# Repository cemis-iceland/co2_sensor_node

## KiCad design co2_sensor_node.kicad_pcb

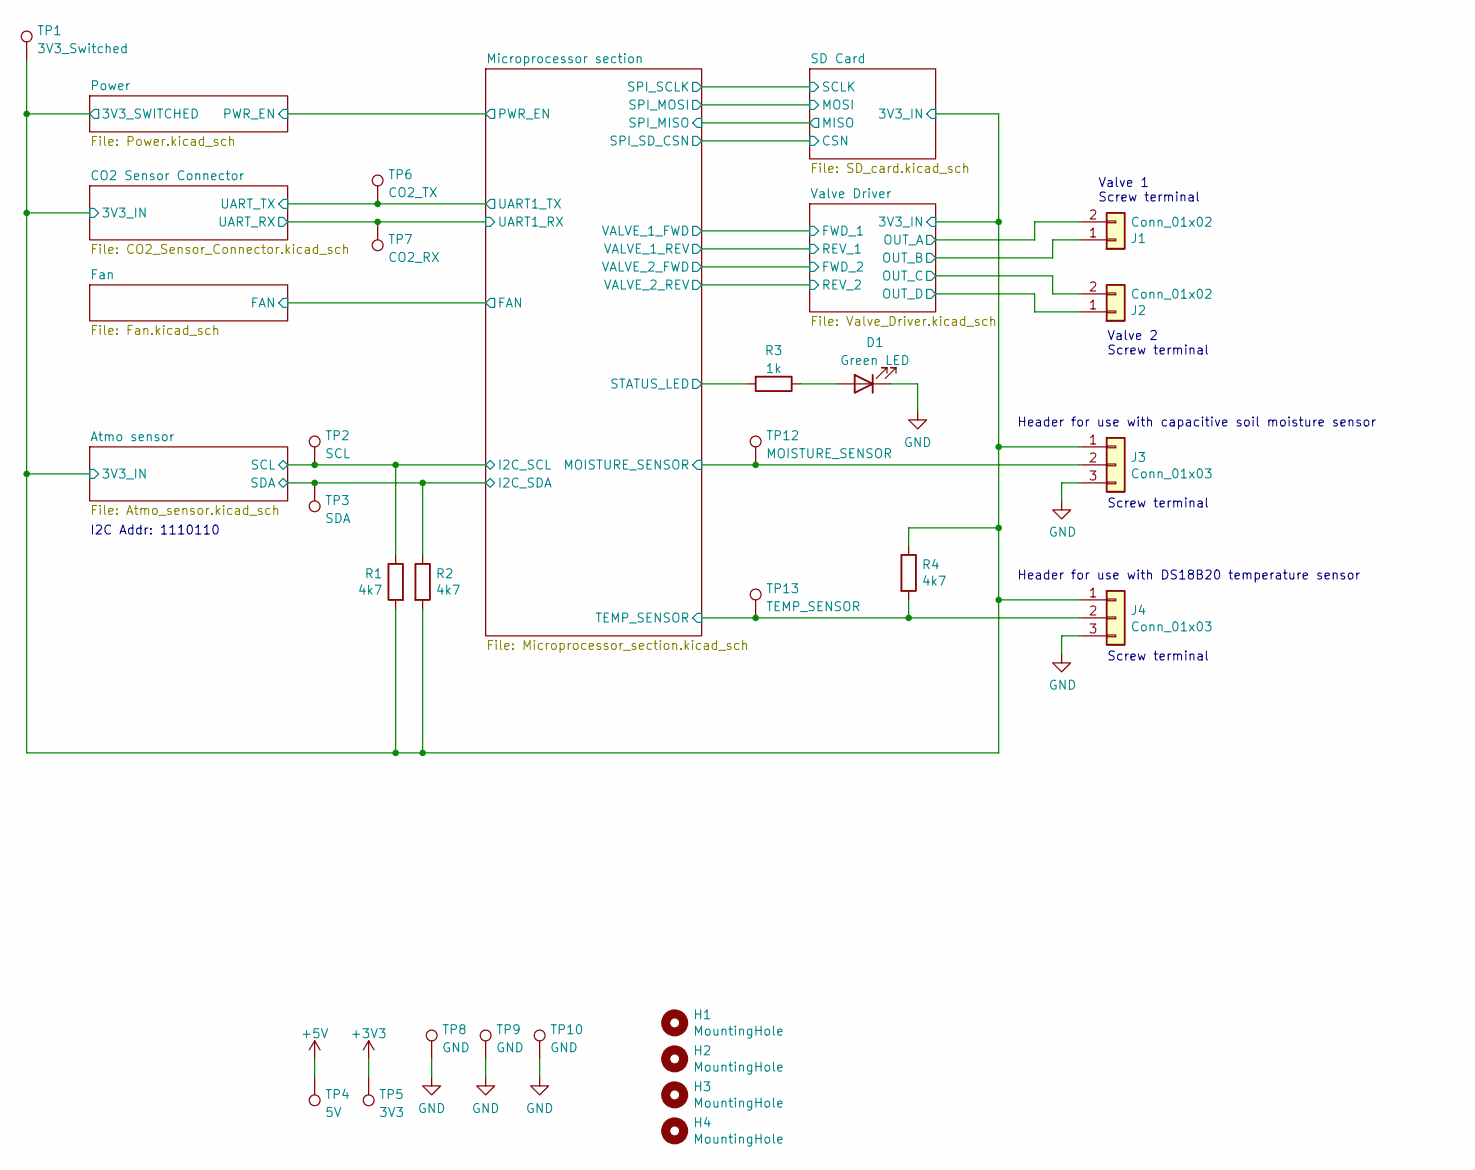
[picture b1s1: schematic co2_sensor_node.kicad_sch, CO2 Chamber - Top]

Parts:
D1: Green LED; LED_0603_1608Metric; LCSC C72043
H1, H2, H3, H4: MountingHole; MountingHole_3.2mm_M3
J1, J2: Conn_01x02; KF301-5.0-2P; LCSC C474881
J3, J4: Conn_01x03; KF301-5.0-3P; LCSC C474882
R1, R2, R4: 4k7; R_0603_1608Metric; LCSC C23162
R3: 1k; R_0603_1608Metric; LCSC C21190
TP1: 3V3_Switched; TestPoint_Loop_D2.50mm_Drill1.0mm_LowProfile
TP2: SCL; TestPoint_Loop_D2.50mm_Drill1.0mm_LowProfile
TP3: SDA; TestPoint_Loop_D2.50mm_Drill1.0mm_LowProfile
TP4: 5V; TestPoint_Loop_D2.50mm_Drill1.0mm_LowProfile
TP5: 3V3; TestPoint_Loop_D2.50mm_Drill1.0mm_LowProfile
TP6: CO2_TX; TestPoint_Loop_D2.50mm_Drill1.0mm_LowProfile
TP7: CO2_RX; TestPoint_Loop_D2.50mm_Drill1.0mm_LowProfile
TP8, TP9, TP10: GND; TestPoint_Loop_D2.50mm_Drill1.0mm_LowProfile
TP12: MOISTURE_SENSOR; TestPoint_Loop_D2.50mm_Drill1.0mm_LowProfile
TP13: TEMP_SENSOR; TestPoint_Loop_D2.50mm_Drill1.0mm_LowProfile

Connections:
+3V3: TP5.1; also elsewhere on the board
+5V: TP4.1; also elsewhere on the board
/Atmo sensor/3V3_IN: J3.1, J4.1, R1.2, R2.2, R4.1, TP1.1; also elsewhere on the board
/Atmo sensor/SCL: R1.1, TP2.1; also elsewhere on the board
/Atmo sensor/SDA: R2.1, TP3.1; also elsewhere on the board
/CO2 Sensor Connector/UART_RX: TP7.1; also elsewhere on the board
/CO2 Sensor Connector/UART_TX: TP6.1; also elsewhere on the board
/Microprocessor section/MOISTURE_SENSOR: J3.2, TP12.1; also elsewhere on the board
/Microprocessor section/STATUS_LED: R3.2; also elsewhere on the board
/Microprocessor section/TEMP_SENSOR: J4.2, R4.2, TP13.1; also elsewhere on the board
/Valve Driver/OUT_A: J1.2; also elsewhere on the board
/Valve Driver/OUT_B: J1.1; also elsewhere on the board
/Valve Driver/OUT_C: J2.2; also elsewhere on the board
/Valve Driver/OUT_D: J2.1; also elsewhere on the board
GND: D1.1 (K), J3.3, J4.3, TP8.1, TP9.1, TP10.1; also elsewhere on the board
unnamed: D1.2 (A), R3.1

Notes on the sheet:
I2C Addr: 1110110
Header for use with capacitive soil moisture sensor
Header for use with DS18B20 temperature sensor
Screw terminal
Valve 1 Screw terminal
Valve 2 Screw terminal

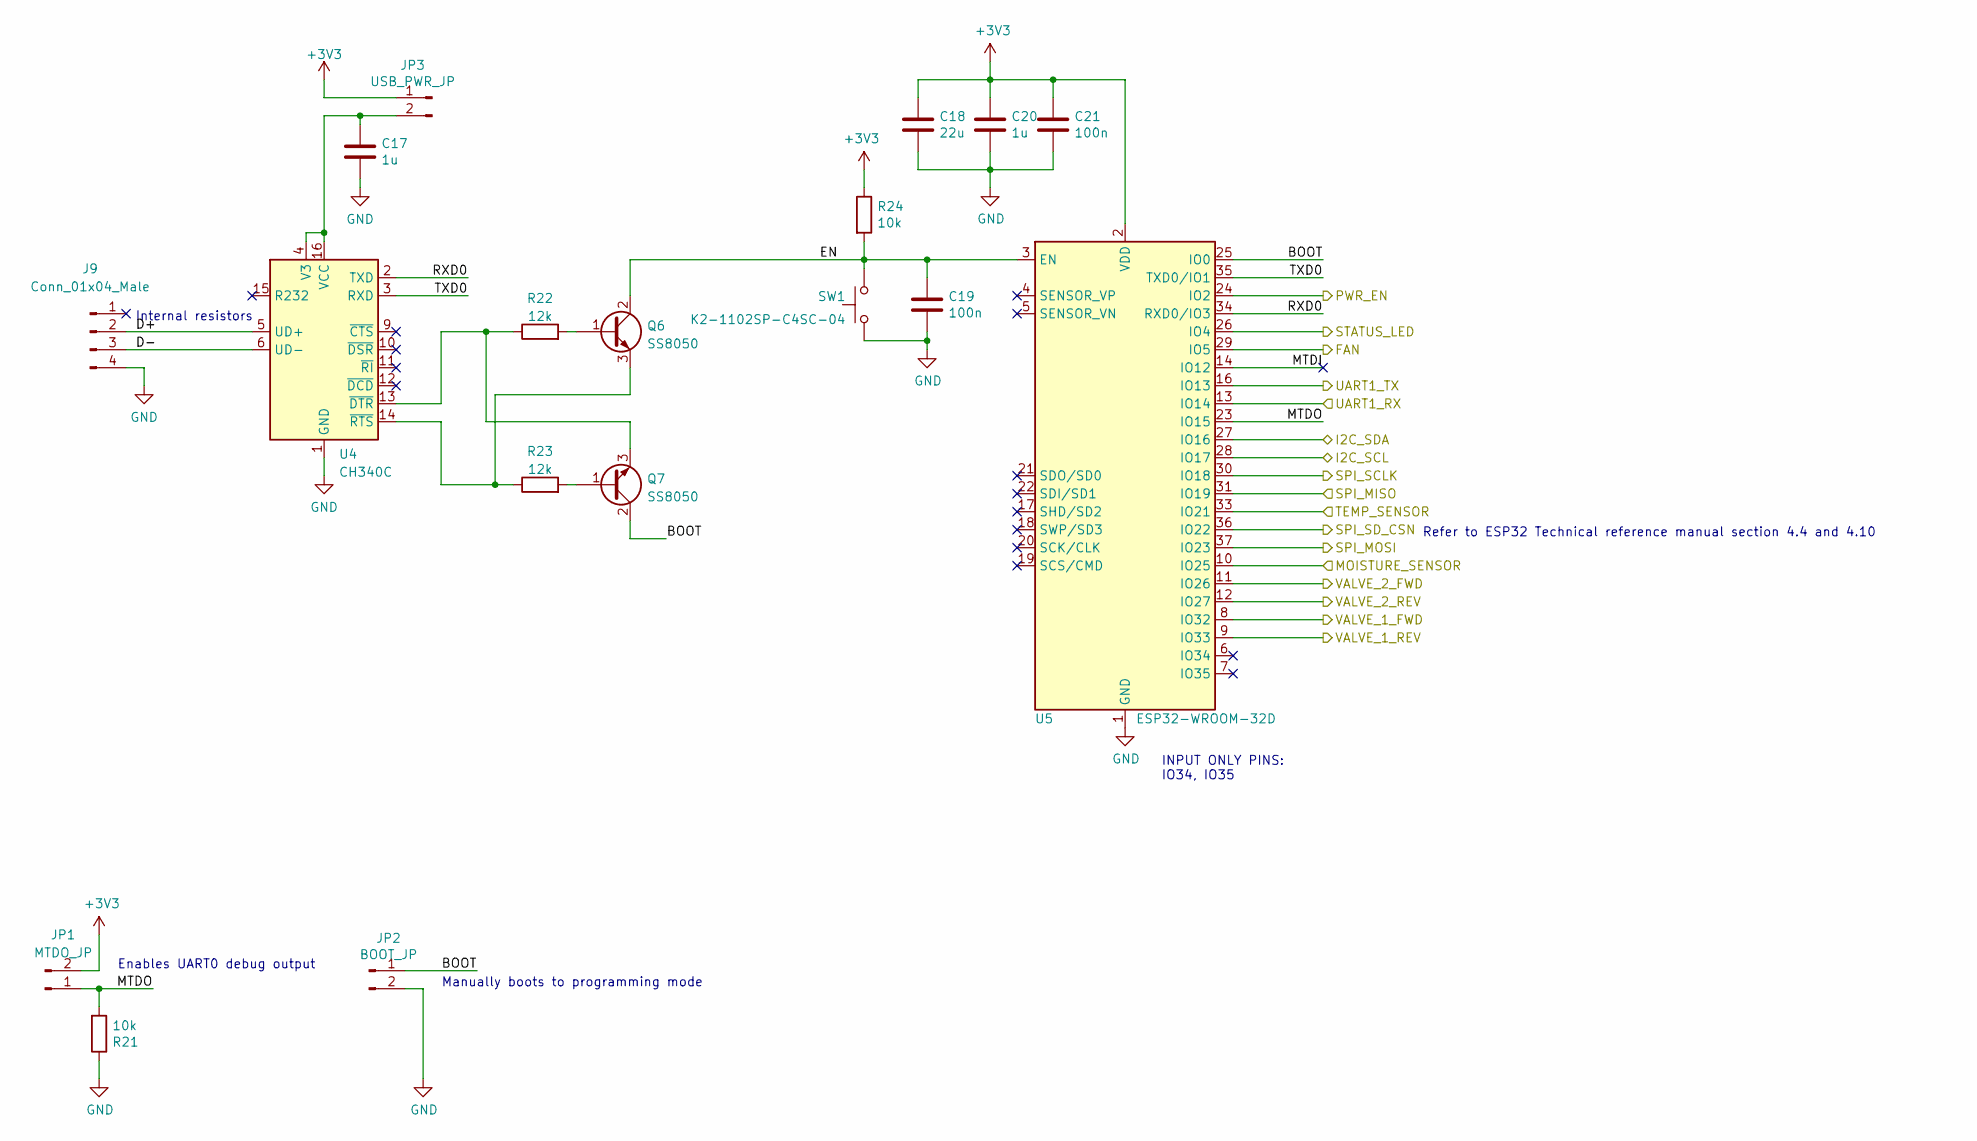
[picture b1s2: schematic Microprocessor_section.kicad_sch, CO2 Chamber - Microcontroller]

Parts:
C17, C20: 1u; C_0603_1608Metric; LCSC C15849
C18: 22u; C_0805_2012Metric; LCSC C45783
C19, C21: 100n; C_0603_1608Metric; LCSC C14663
J9: Conn_01x04_Male; PinHeader_1x04_P2.54mm_Vertical; LCSC C492403
JP1: MTDO_JP; PinHeader_1x02_P2.54mm_Vertical; LCSC C160332
JP2: BOOT_JP; PinHeader_1x02_P2.54mm_Vertical; LCSC C160332
JP3: USB_PWR_JP; PinHeader_1x02_P2.54mm_Vertical; LCSC C160332
Q6, Q7: SS8050; SOT-23; LCSC C2150
R21, R24: 10k; R_0603_1608Metric; LCSC C25804
R22, R23: 12k; R_0603_1608Metric; LCSC C22790
SW1: K2-1102SP-C4SC-04; K2-1102SP-xxxC; LCSC C127509
U4: CH340C; SOIC-16_3.9x9.9mm_P1.27mm; LCSC C84681
U5: ESP32-WROOM-32D; ESP32-WROOM-32; LCSC C473012

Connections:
+3V3: C18.1, C20.1, C21.1, JP1.2, JP3.1, R24.1, U5.2 (VDD); also elsewhere on the board
/Atmo sensor/SCL: U5.28 (IO17); also elsewhere on the board
/Atmo sensor/SDA: U5.27 (IO16); also elsewhere on the board
/CO2 Sensor Connector/UART_RX: U5.13 (IO14); also elsewhere on the board
/CO2 Sensor Connector/UART_TX: U5.16 (IO13); also elsewhere on the board
/Fan/FAN: U5.29 (IO5); also elsewhere on the board
/Microprocessor section/BOOT: JP2.1, Q7.2 (C), U5.25 (IO0)
/Microprocessor section/D+: J9.2, U4.5 (UD+)
/Microprocessor section/D-: J9.3, U4.6 (UD-)
/Microprocessor section/EN: C19.1, Q6.2 (C), R24.2, SW1.2, U5.3 (EN)
/Microprocessor section/MOISTURE_SENSOR: U5.10 (IO25); also elsewhere on the board
/Microprocessor section/MTDI: U5.14 (IO12)
/Microprocessor section/MTDO: JP1.1, R21.2, U5.23 (IO15)
/Microprocessor section/PWR_EN: U5.24 (IO2); also elsewhere on the board
/Microprocessor section/RXD0: U4.2 (TXD), U5.34 (RXD0/IO3)
/Microprocessor section/SPI_MISO: U5.31 (IO19); also elsewhere on the board
/Microprocessor section/SPI_MOSI: U5.37 (IO23); also elsewhere on the board
/Microprocessor section/SPI_SCLK: U5.30 (IO18); also elsewhere on the board
/Microprocessor section/SPI_SD_CSN: U5.36 (IO22); also elsewhere on the board
/Microprocessor section/STATUS_LED: U5.26 (IO4); also elsewhere on the board
/Microprocessor section/TEMP_SENSOR: U5.33 (IO21); also elsewhere on the board
/Microprocessor section/TXD0: U4.3 (RXD), U5.35 (TXD0/IO1)
/Microprocessor section/VALVE_1_FWD: U5.8 (IO32); also elsewhere on the board
/Microprocessor section/VALVE_1_REV: U5.9 (IO33); also elsewhere on the board
/Microprocessor section/VALVE_2_FWD: U5.11 (IO26); also elsewhere on the board
/Microprocessor section/VALVE_2_REV: U5.12 (IO27); also elsewhere on the board
GND: C17.2, C18.2, C19.2, C20.2, C21.2, J9.4, JP2.2, R21.1, SW1.1, U4.1 (GND), U5.1 (GND), U5.15 (GND), U5.38 (GND), U5.39 (GND); also elsewhere on the board
unnamed: C17.1, JP3.2, U4.4 (V3), U4.16 (VCC)
unnamed: Q6.1 (B), R22.2
unnamed: Q6.3 (E), R23.1, U4.14 (~RTS)
unnamed: Q7.1 (B), R23.2
unnamed: Q7.3 (E), R22.1, U4.13 (~DTR)

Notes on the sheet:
INPUT ONLY PINS: IO34, IO35
Refer to ESP32 Technical reference manual section 4.4 and 4.10
Internal resistors
Manually boots to programming mode
Enables UART0 debug output

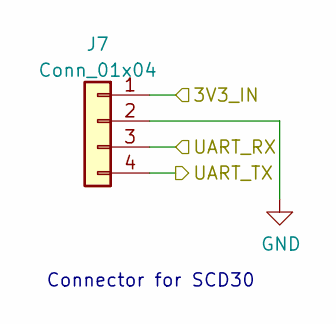
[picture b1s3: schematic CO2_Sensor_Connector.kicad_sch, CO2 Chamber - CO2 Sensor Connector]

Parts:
J7: Conn_01x04; JST_XH_B4B-XH-A_1x04_P2.50mm_Vertical; LCSC C37815

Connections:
/Atmo sensor/3V3_IN: J7.1; also elsewhere on the board
/CO2 Sensor Connector/UART_RX: J7.3; also elsewhere on the board
/CO2 Sensor Connector/UART_TX: J7.4; also elsewhere on the board
GND: J7.2; also elsewhere on the board

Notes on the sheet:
Connector for SCD30

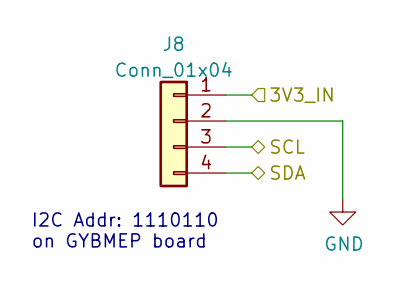
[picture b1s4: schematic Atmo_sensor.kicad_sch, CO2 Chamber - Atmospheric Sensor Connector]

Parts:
J8: Conn_01x04; JST_XH_B4B-XH-A_1x04_P2.50mm_Vertical; LCSC C37815

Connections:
/Atmo sensor/3V3_IN: J8.1; also elsewhere on the board
/Atmo sensor/SCL: J8.3; also elsewhere on the board
/Atmo sensor/SDA: J8.4; also elsewhere on the board
GND: J8.2; also elsewhere on the board

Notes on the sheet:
I2C Addr: 1110110 on GYBMEP board

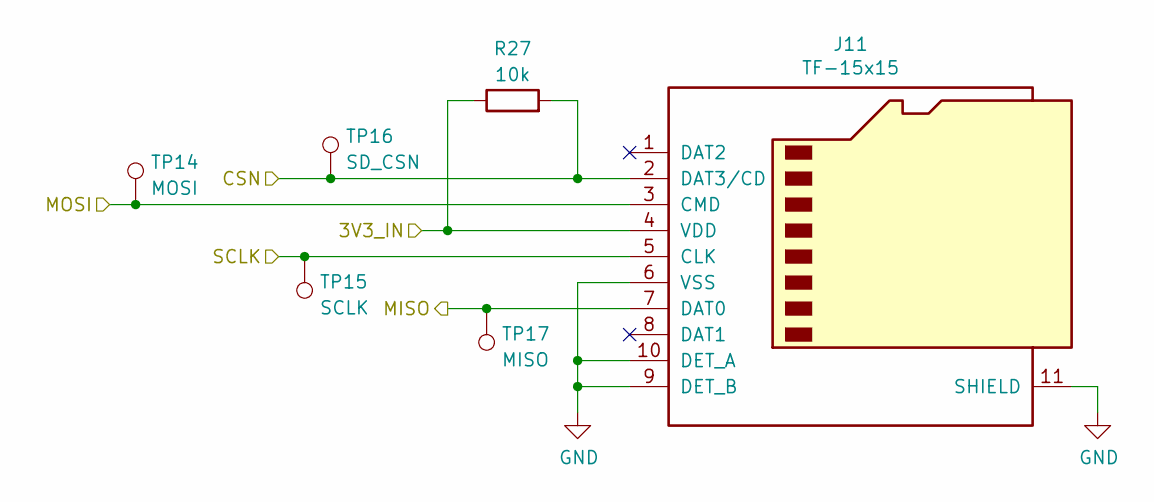
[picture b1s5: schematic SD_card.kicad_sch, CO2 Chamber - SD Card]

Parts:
J11: TF-15x15; LCSC C111196
R27: 10k; R_0603_1608Metric; LCSC C25804
TP14: MOSI; TestPoint_Loop_D2.50mm_Drill1.0mm_LowProfile
TP15: SCLK; TestPoint_Loop_D2.50mm_Drill1.0mm_LowProfile
TP16: SD_CSN; TestPoint_Loop_D2.50mm_Drill1.0mm_LowProfile
TP17: MISO; TestPoint_Loop_D2.50mm_Drill1.0mm_LowProfile

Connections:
/Atmo sensor/3V3_IN: J11.4 (VDD), R27.1; also elsewhere on the board
/Microprocessor section/SPI_MISO: J11.7 (DAT0), TP17.1; also elsewhere on the board
/Microprocessor section/SPI_MOSI: J11.3 (CMD), TP14.1; also elsewhere on the board
/Microprocessor section/SPI_SCLK: J11.5 (CLK), TP15.1; also elsewhere on the board
/Microprocessor section/SPI_SD_CSN: J11.2 (DAT3/CD), R27.2, TP16.1; also elsewhere on the board
GND: J11.6 (VSS), J11.9 (DET_B), J11.10 (DET_A), J11.11 (SHIELD); also elsewhere on the board

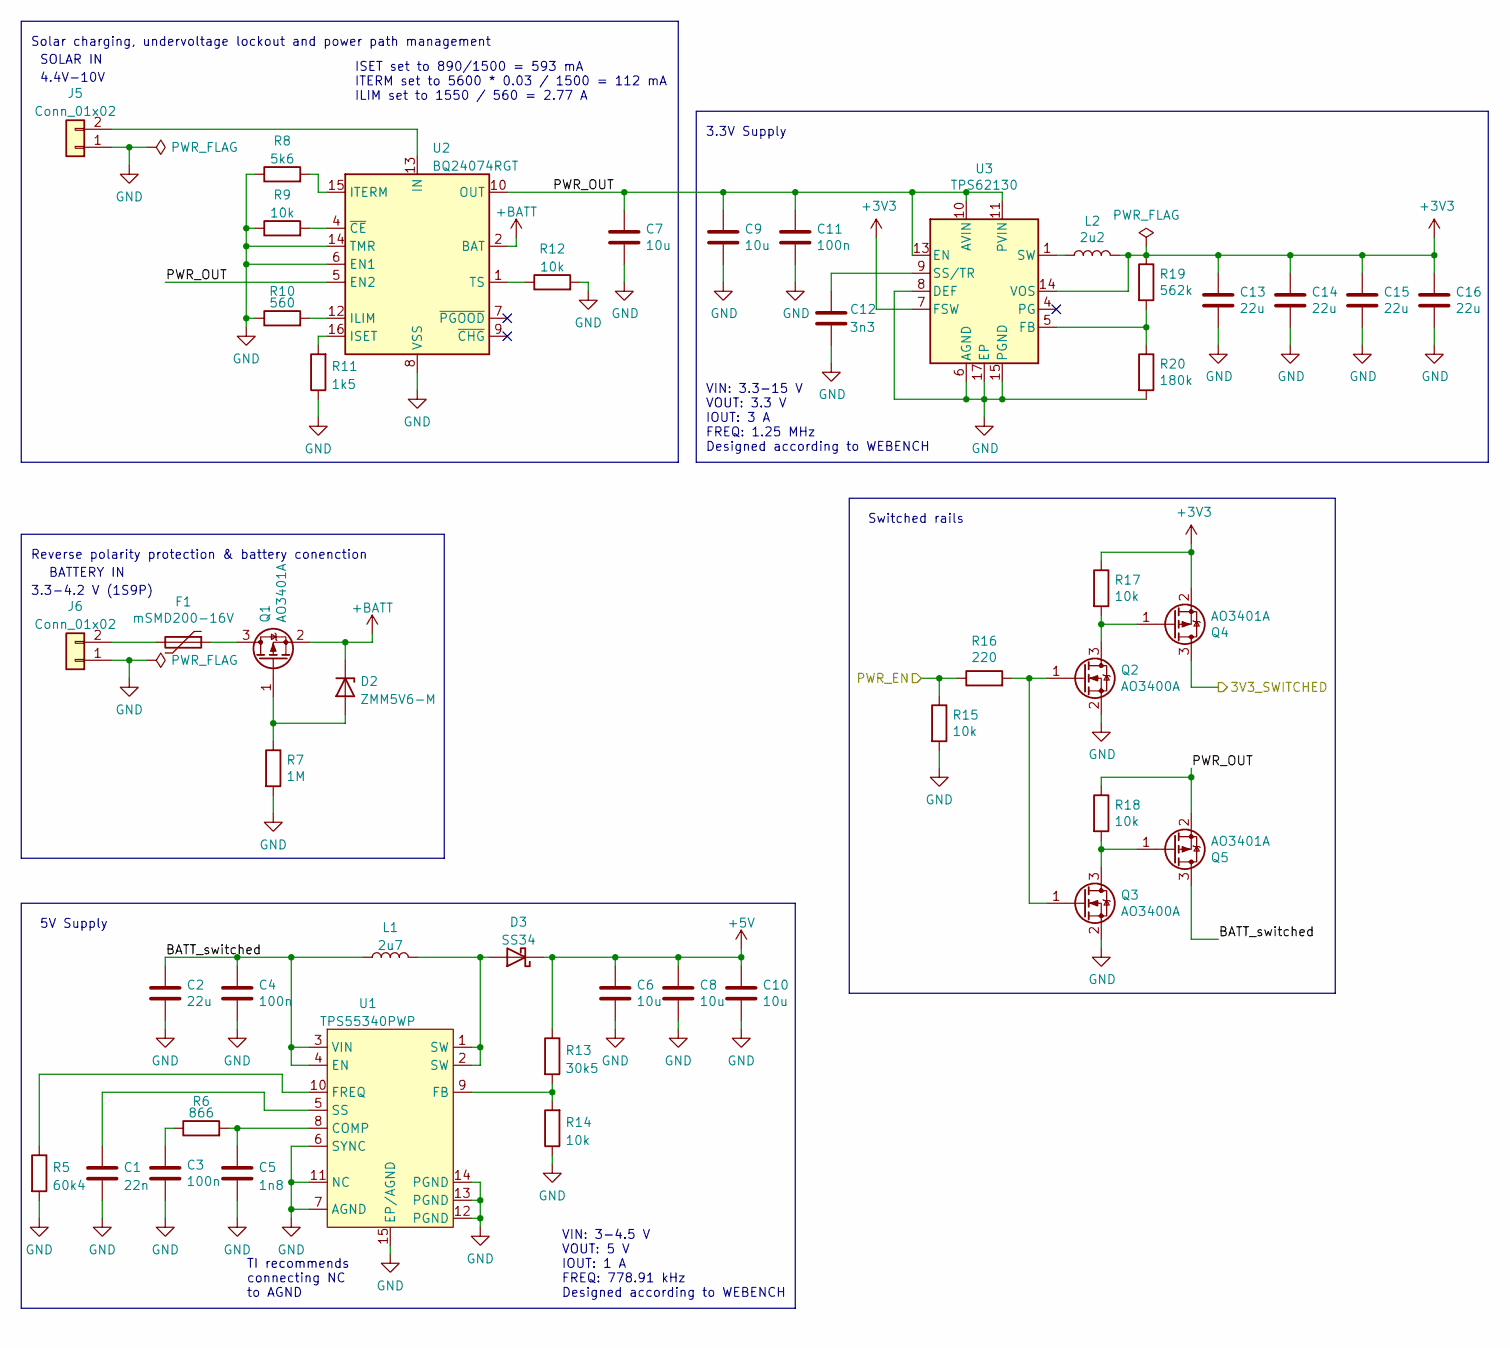
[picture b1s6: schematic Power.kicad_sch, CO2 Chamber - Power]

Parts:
C1: 22n; C_0603_1608Metric; LCSC C21122
C2, C13, C14, C15, C16: 22u; C_0805_2012Metric; LCSC C45783
C3, C4, C11: 100n; C_0603_1608Metric; LCSC C14663
C5: 1n8; C_0603_1608Metric; LCSC C318642
C6, C7, C8, C9, C10: 10u; C_0805_2012Metric; LCSC C15850
C12: 3n3; C_0603_1608Metric; LCSC C1613
D2: ZMM5V6-M; D_MiniMELF; LCSC C8062
D3: SS34; D_SMA; LCSC C8678
F1: mSMD200-16V; Fuse_1812_4532Metric; LCSC C70126
J5, J6: Conn_01x02; JST_XH_B2B-XH-AM_1x02_P2.50mm_Vertical; LCSC C20079
L1: 2u7; PCD0504MT2R7; LCSC C324320
L2: 2u2; WPN4020; LCSC C98361
Q1, Q4, Q5: AO3401A; SOT-23; LCSC C15127
Q2, Q3: AO3400A; SOT-23; LCSC C20917
R5: 60k4; R_0402_1005Metric; LCSC C310240
R6: 866; R_0402_1005Metric; LCSC C227251
R7: 1M; R_0603_1608Metric; LCSC C22935
R8: 5k6; R_0603_1608Metric
R9, R12, R14, R15, R17, R18: 10k; R_0603_1608Metric; LCSC C25804
R10: 560; R_0603_1608Metric
R11: 1k5; R_0603_1608Metric
R13: 30k5; R_0402_1005Metric; LCSC C185428
R16: 220; R_0603_1608Metric; LCSC C22962
R19: 562k; R_0603_1608Metric; LCSC C23205
R20: 180k; R_0603_1608Metric; LCSC C22827
U1: TPS55340PWP; HTSSOP-14-1EP_4.4x5mm_P0.65mm_EP3.4x5mm_Mask3x3.1mm_Thermal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; LCSC C43862
U2: BQ24074RGT; VQFN-16-1EP_3x3mm_P0.5mm_EP1.6x1.6mm; LCSC C54313
U3: TPS62130; VQFN-16-1EP_3x3mm_P0.5mm_EP1.68x1.68mm_ThermalVias; LCSC C43590

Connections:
+3V3: C13.1, C14.1, C15.1, C16.1, L2.2, Q4.2 (S), R17.1, R19.1, U3.7 (FSW), U3.14 (VOS); also elsewhere on the board
+5V: C6.1, C8.1, C10.1, D3.1 (K), R13.1; also elsewhere on the board
+BATT: D2.1 (K), Q1.2 (S), U2.2 (BAT), U2.3 (BAT)
/Atmo sensor/3V3_IN: Q4.3 (D); also elsewhere on the board
/Microprocessor section/PWR_EN: R15.1, R16.1; also elsewhere on the board
/Power/BATT_switched: C2.1, C4.1, L1.1, Q5.3 (D), U1.3 (VIN), U1.4 (EN)
/Power/PWR_OUT: C7.1, C9.1, C11.1, Q5.2 (S), R18.1, U2.5 (EN2), U2.10 (OUT), U2.11 (OUT), U3.10 (AVIN), U3.11 (PVIN), U3.12 (PVIN), U3.13 (EN)
GND: C1.2, C2.2, C3.2, C4.2, C5.2, C6.2, C7.2, C8.2, C9.2, C10.2, C11.2, C12.2, C13.2, C14.2, C15.2, C16.2, J5.1, J6.1, Q2.2 (S), Q3.2 (S), R5.2, R7.2, R8.1, R9.1, R10.1, R11.1, R12.2, R14.1, R15.2, R20.2, U1.6 (SYNC), U1.7 (AGND), U1.11 (NC), U1.12 (PGND), U1.13 (PGND), U1.14 (PGND), U1.15 (EP/AGND), U2.6 (EN1), U2.8 (VSS), U2.14 (TMR), U2.17 (VSS), U3.6 (AGND), U3.8 (DEF), U3.15 (PGND), U3.16 (PGND), U3.17 (EP); also elsewhere on the board
unnamed: C1.1, U1.5 (SS)
unnamed: C3.1, R6.1
unnamed: C5.1, R6.2, U1.8 (COMP)
unnamed: C12.1, U3.9 (SS/TR)
unnamed: D2.2 (A), Q1.1 (G), R7.1
unnamed: D3.2 (A), L1.2, U1.1 (SW), U1.2 (SW)
unnamed: F1.1, Q1.3 (D)
unnamed: F1.2, J6.2
unnamed: J5.2, U2.13 (IN)
unnamed: L2.1, U3.1 (SW), U3.2 (SW), U3.3 (SW)
unnamed: Q2.1 (G), Q3.1 (G), R16.2
unnamed: Q2.3 (D), Q4.1 (G), R17.2
unnamed: Q3.3 (D), Q5.1 (G), R18.2
unnamed: R5.1, U1.10 (FREQ)
unnamed: R8.2, U2.15 (ITERM)
unnamed: R9.2, U2.4 (~CE)
unnamed: R10.2, U2.12 (ILIM)
unnamed: R11.2, U2.16 (ISET)
unnamed: R12.1, U2.1 (TS)
unnamed: R13.2, R14.2, U1.9 (FB)
unnamed: R19.2, R20.1, U3.5 (FB)

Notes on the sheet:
VIN: 3.3-15 V VOUT: 3.3 V IOUT: 3 A FREQ: 1.25 MHz Designed according to WEBENCH
BATTERY IN
5V Supply
4.4V-10V
Solar charging, undervoltage lockout and power path management
3.3-4.2 V (1S9P)
3.3V Supply
Reverse polarity protection & battery conenction
SOLAR IN
ISET set to 890/1500 = 593 mA ITERM set to 5600 * 0.03 / 1500 = 112 mA ILIM set to 1550 / 560 = 2.77 A
VIN: 3-4.5 V VOUT: 5 V IOUT: 1 A FREQ: 778.91 kHz Designed according to WEBENCH
TI recommends connecting NC to AGND
Switched rails

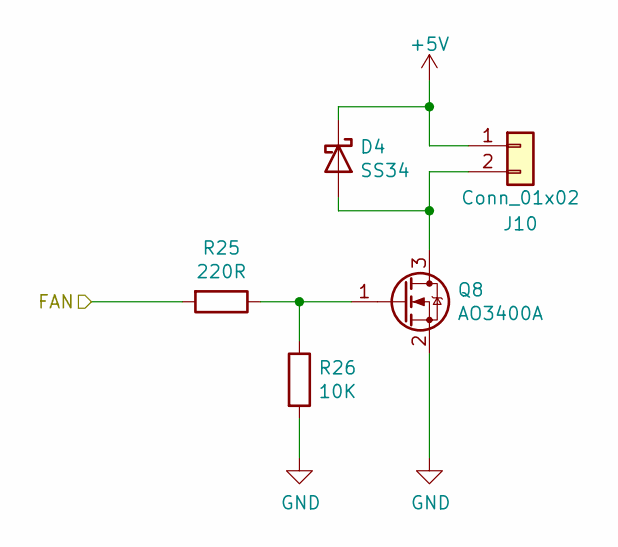
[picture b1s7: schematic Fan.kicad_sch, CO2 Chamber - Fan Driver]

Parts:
D4: SS34; D_SMA; LCSC C8678
J10: Conn_01x02; JST_XH_B2B-XH-AM_1x02_P2.50mm_Vertical; LCSC C20079
Q8: AO3400A; SOT-23; LCSC C20917
R25: 220R; R_0603_1608Metric
R26: 10K; R_0603_1608Metric

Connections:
+5V: D4.1 (K), J10.1; also elsewhere on the board
/Fan/FAN: R25.2; also elsewhere on the board
GND: Q8.2 (S), R26.2; also elsewhere on the board
unnamed: D4.2 (A), J10.2, Q8.3 (D)
unnamed: Q8.1 (G), R25.1, R26.1

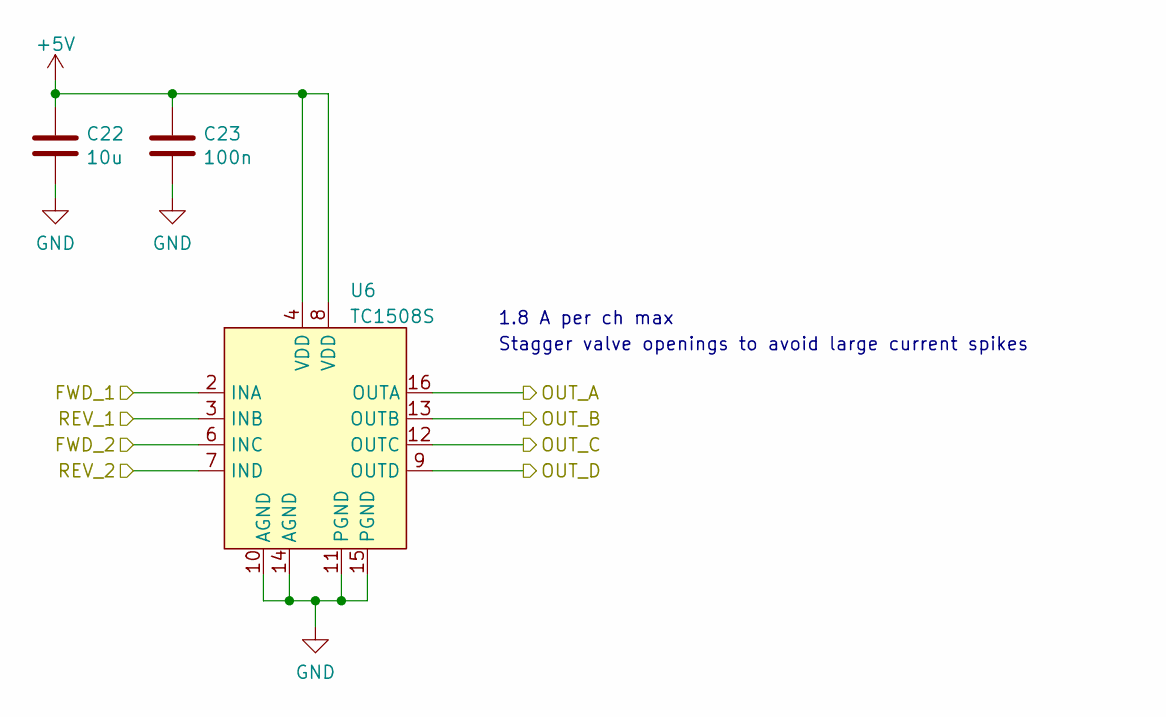
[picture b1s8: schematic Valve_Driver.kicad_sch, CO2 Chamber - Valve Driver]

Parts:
C22: 10u; C_0805_2012Metric; LCSC C15850
C23: 100n; C_0603_1608Metric; LCSC C14663
U6: TC1508S; SOP-16_3.9x9.9mm_P1.27mm; LCSC C89480

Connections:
+5V: C22.1, C23.1, U6.4 (VDD), U6.8 (VDD); also elsewhere on the board
/Microprocessor section/VALVE_1_FWD: U6.2 (INA); also elsewhere on the board
/Microprocessor section/VALVE_1_REV: U6.3 (INB); also elsewhere on the board
/Microprocessor section/VALVE_2_FWD: U6.6 (INC); also elsewhere on the board
/Microprocessor section/VALVE_2_REV: U6.7 (IND); also elsewhere on the board
/Valve Driver/OUT_A: U6.16 (OUTA); also elsewhere on the board
/Valve Driver/OUT_B: U6.13 (OUTB); also elsewhere on the board
/Valve Driver/OUT_C: U6.12 (OUTC); also elsewhere on the board
/Valve Driver/OUT_D: U6.9 (OUTD); also elsewhere on the board
GND: C22.2, C23.2, U6.10 (AGND), U6.11 (PGND), U6.14 (AGND), U6.15 (PGND); also elsewhere on the board

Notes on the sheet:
1.8 A per ch max
Stagger valve openings to avoid large current spikes

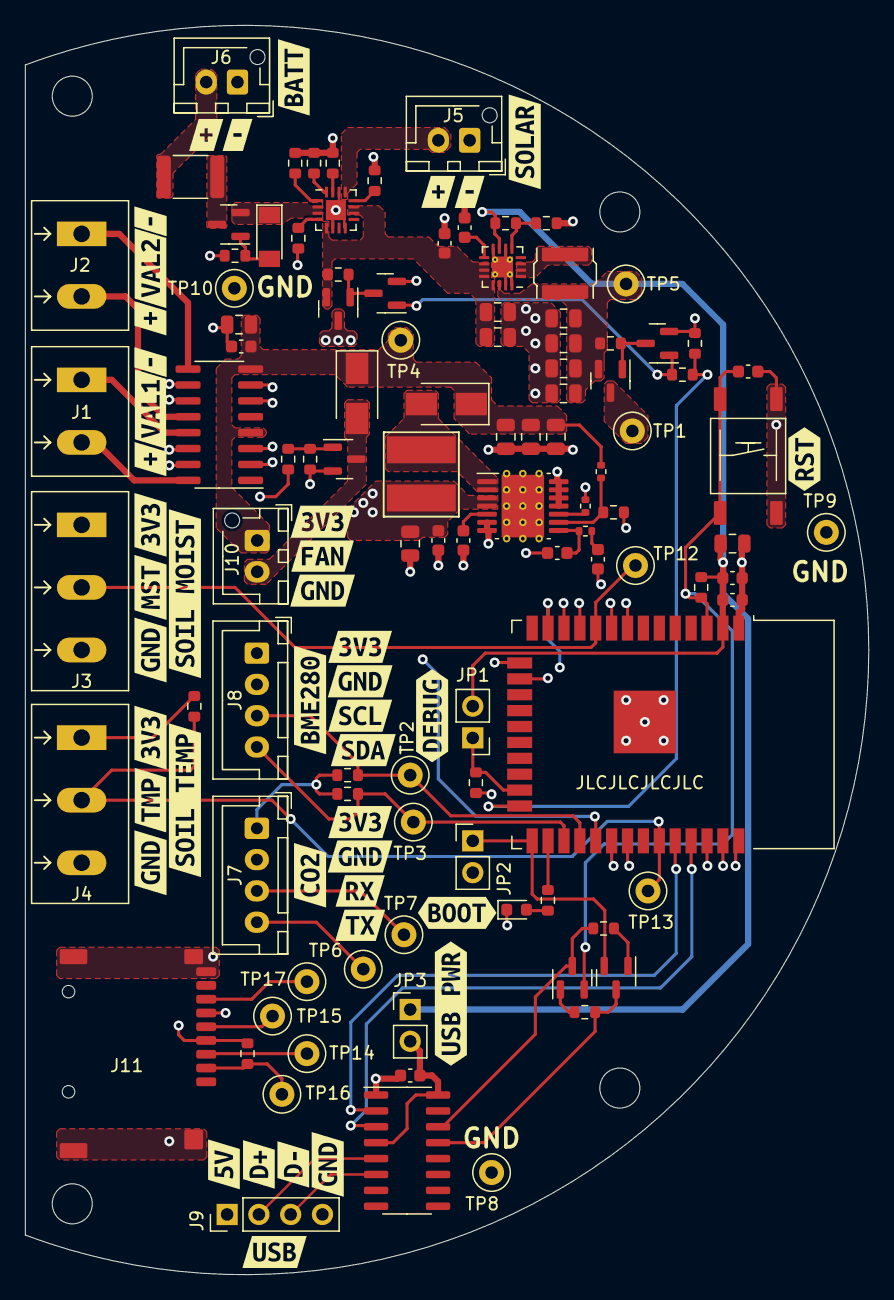
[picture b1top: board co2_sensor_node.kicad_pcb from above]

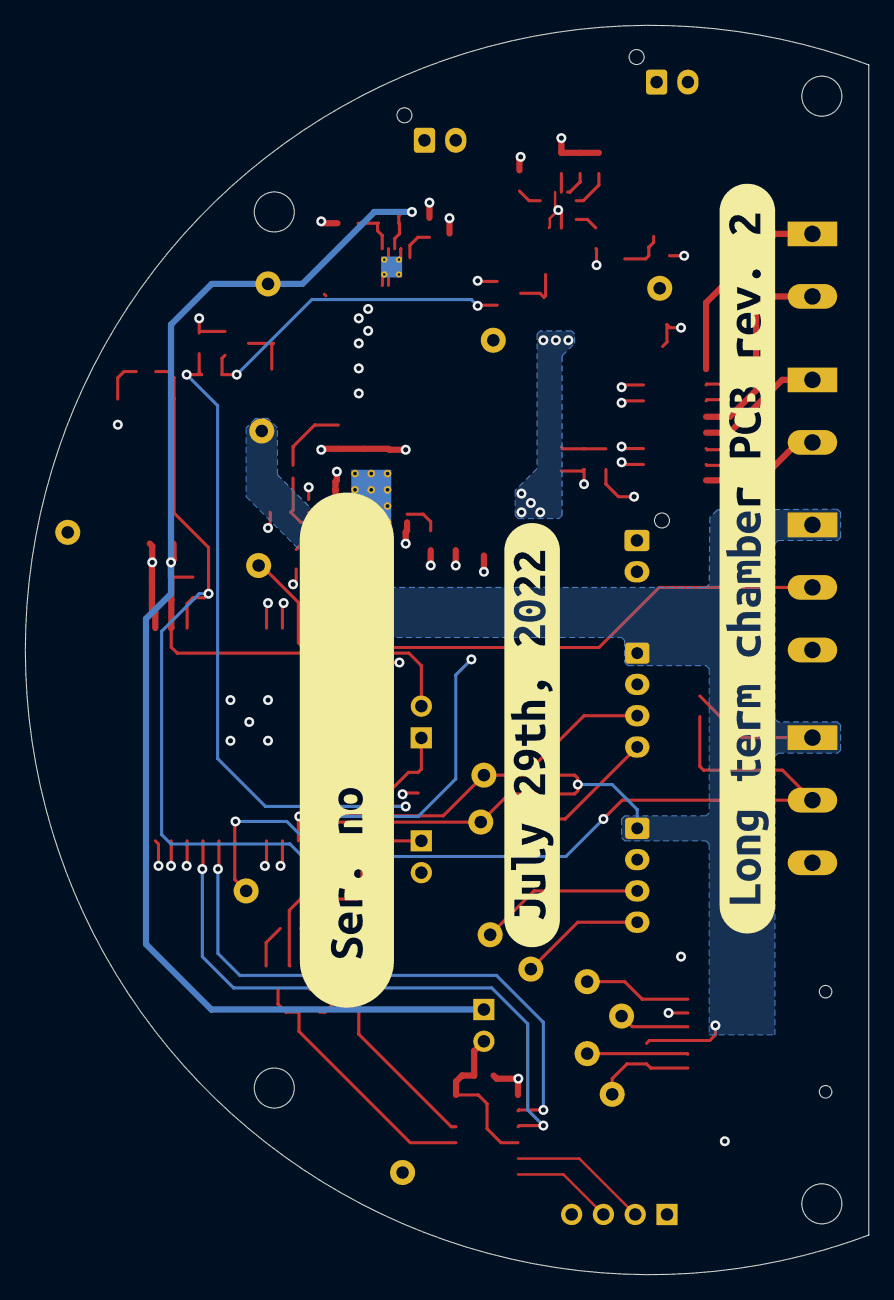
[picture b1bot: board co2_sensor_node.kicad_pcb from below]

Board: 4 copper layers, 67.4 x 99.8 mm, 151 parts (3 on the bottom side), 64 nets.

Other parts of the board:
kibuzzard-62D933FC: G***; kibuzzard-62D933FC
kibuzzard-62D936A1: G***; kibuzzard-62D936A1
kibuzzard-62D936BA: G***; kibuzzard-62D936BA
kibuzzard-62D936C1: G***; kibuzzard-62D936C1
kibuzzard-62D936C8: G***; kibuzzard-62D936C8
kibuzzard-62D936D1: G***; kibuzzard-62D936D1
kibuzzard-62D95196: G***; kibuzzard-62D95196
kibuzzard-62E4018B: G***; kibuzzard-62E4018B
kibuzzard-62E4020F: G***; kibuzzard-62E4020F
kibuzzard-62E91481: G***; kibuzzard-62E91481
kibuzzard-628CFF9F: G***; kibuzzard-628CFF9F
kibuzzard-628CFF95: G***; kibuzzard-628CFF95
kibuzzard-628CFFA6: G***; kibuzzard-628CFFA6
kibuzzard-628CFFAE: G***; kibuzzard-628CFFAE
kibuzzard-628CFFC0: G***; kibuzzard-628CFFC0
kibuzzard-628CFFCE: G***; kibuzzard-628CFFCE
kibuzzard-628D01AC: G***; kibuzzard-628D01AC
kibuzzard-628D01D9: G***; kibuzzard-628D01D9
kibuzzard-628D06EC: G***; kibuzzard-628D06EC
kibuzzard-628D076D, kibuzzard-628D076D#2, kibuzzard-628D076D#3, kibuzzard-628D076D#4: G***; kibuzzard-628D076D
kibuzzard-628D082D: G***; kibuzzard-628D082D
kibuzzard-628D085C: G***; kibuzzard-628D085C
kibuzzard-628D086F: G***; kibuzzard-628D086F
kibuzzard-628D087A: G***; kibuzzard-628D087A
kibuzzard-628D090E: G***; kibuzzard-628D090E
kibuzzard-628D091C: G***; kibuzzard-628D091C
kibuzzard-628D0108: G***; kibuzzard-628D0108
kibuzzard-628D0120: G***; kibuzzard-628D0120
kibuzzard-628D0190: G***; kibuzzard-628D0190
kibuzzard-628D0781, kibuzzard-628D0781#2, kibuzzard-628D0781#3, kibuzzard-628D0781#4: G***; kibuzzard-628D0781
kibuzzard-628D0804: G***; kibuzzard-628D0804
kibuzzard-628D0814: G***; kibuzzard-628D0814
kibuzzard-628D0827: G***; kibuzzard-628D0827
kibuzzard-628D0915: G***; kibuzzard-628D0915
kibuzzard-628D0922: G***; kibuzzard-628D0922
kibuzzard-628D0934: G***; kibuzzard-628D0934
kibuzzard-628E3C8D: G***; kibuzzard-628E3C8D
kibuzzard-628E3C65: G***; kibuzzard-628E3C65
kibuzzard-629F65FE: G***; kibuzzard-629F65FE

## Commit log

2021-05-19 initial
2021-05-19 Change mcp reset pin cap to 100n, add uart2 lines
2021-05-19 Design CO2 sensor connector
    Connectors for the SCD30 and the K30FR.
    Including high side load switch.
2021-05-19 Fix atmo sensor, add LoRa schematic
2021-05-19 Rearranged IO connections to take advantage of hardware interfaces where possible
2021-05-21 Connect SD card
2021-05-21 Draw power schematic
2021-05-21 Change BME280 out for connector
2021-05-21 Begin assigning footprints
2021-05-25 Finish attaching footprints for revision 1
2021-05-25 Actually include footprint library
2021-05-25 Start changing buck converters
2021-05-25 Finished revising power section schematic
2021-05-26 Start PCB layout
2021-05-26 First cut at layout
2021-05-27 Start routing power section
2021-05-27 Layout complete, barring review and polish
2021-05-28 Export fabrication files
2021-05-28 Remove csv from gitignore
2021-06-03 Start changing design for long term chambers
2021-06-21 Fix sensor PMOS issue and start change to long term chamber
2021-06-21 Add MPPT battery charger and polyfuse, replace reverse polarity
2021-06-21 Remove all references to 6V supply which has been removed
2021-06-21 Add connector for external chamber connection and change SMA to U.FL connector
2021-06-22 Finalize schematic
2021-07-01 Finish routing of Rev 1
2022-05-13 Remove unused circuits
2022-05-19 Move to KiCad v6, redesign circuit for chamber
2022-05-19 Add test points, add JLC part numbers to JST XH connectors, clean up
2022-05-20 Add testpoint footprint assignments
2022-05-25 Finish PCB layout
2022-05-25 fixed the HOLE by adding rounded corners
2022-05-25 New step model
2022-05-30 Add voltage selection header for fan
2022-05-30 Clean folder up a bit
2022-06-07 Finalize PCB and generate manufacturing files
2022-07-11 Start redesign for rev. 2
2022-07-19 Checkpoint
2022-07-19 Finish rev. 2 schematic and begin PCB layout
2022-07-20 Continued PCB layout
2022-07-26 Add 5V boost converter and begin redesign of PCB
2022-07-27 More layout work
2022-07-28 Finish component placement
2022-07-29 I was never here
2022-07-29 Finish routing PCB revision 2
2022-08-04 Finish routing round 2
